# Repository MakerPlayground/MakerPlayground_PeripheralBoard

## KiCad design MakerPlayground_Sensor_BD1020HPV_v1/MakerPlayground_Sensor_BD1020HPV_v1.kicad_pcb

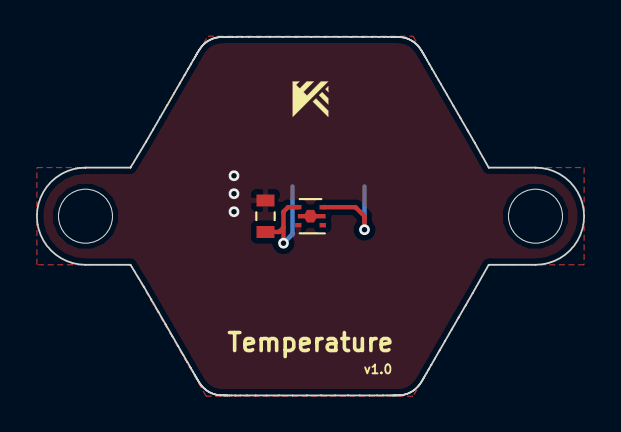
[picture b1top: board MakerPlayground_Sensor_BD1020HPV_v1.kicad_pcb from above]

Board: 2 copper layers, 30.4 x 19.9 mm, 3 parts (1 on the bottom side), 3 nets.

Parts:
C1: 0.1uF; C_0603_1608Metric
J1: Conn_01x04; JST_PH_S4B-PH-SM4-TB_1x04-1MP_P2.00mm_Horizontal
U1: BD1020HFV; HVSOF5

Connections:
GND: C1.2, J1.1, U1.5
unnamed: J1.4, U1.3
VCC: C1.1, J1.2, U1.4

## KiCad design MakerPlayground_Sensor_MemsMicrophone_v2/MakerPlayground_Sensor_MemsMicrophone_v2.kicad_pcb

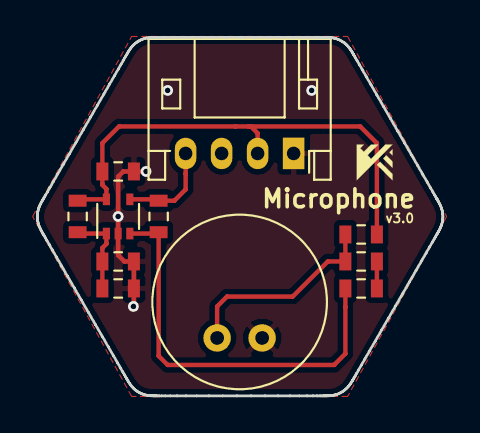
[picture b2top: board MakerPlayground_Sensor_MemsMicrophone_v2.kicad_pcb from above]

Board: 2 copper layers, 22.5 x 19.9 mm, 11 parts (0 on the bottom side), 7 nets.

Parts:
C4, C5: 4.7uF; C_0603_1608Metric
C7: 0.1uF; C_0603_1608Metric
J1: Conn_01x04; JST_PH_S4B-PH-K_1x04_P2.00mm_Horizontal
MK1: 9.7mm; Condenser_Microphone_9.7mm
R1, R2, R3: 10K; R_0603_1608Metric
R4: 820K; R_0603_1608Metric
R5: 2K; R_0603_1608Metric
U2: BD5291FVE-GTR; SOT-353_SC-70-5

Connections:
GND: C5.1, C7.1, J1.1, MK1.2, R3.2, U2.2
unnamed: C4.1, R1.2
unnamed: C4.2, MK1.1, R5.2
unnamed: C5.2, R2.2, R3.1, U2.1
unnamed: R1.1, R4.2, U2.3
Signal: J1.4, R4.1, U2.4
VCC: C7.2, J1.2, R2.1, R5.1, U2.5

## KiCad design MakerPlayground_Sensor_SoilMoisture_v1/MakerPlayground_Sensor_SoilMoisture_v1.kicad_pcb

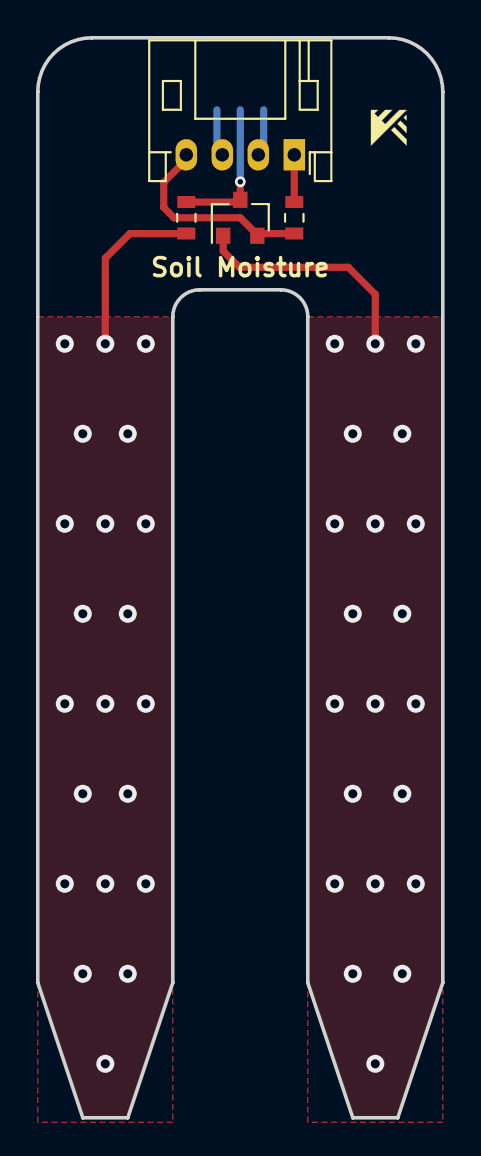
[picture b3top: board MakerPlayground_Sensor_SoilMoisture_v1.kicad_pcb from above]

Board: 2 copper layers, 22.5 x 60.0 mm, 5 parts (1 on the bottom side), 5 nets.

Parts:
J1: Conn_01x04; JST_PH_S4B-PH-K_1x04_P2.00mm_Horizontal
JP1: POWER_SEL; SolderJumper-3_P1.3mm_Bridged12_Pad1.0x1.5mm
Q1: MMBT2222ALT1G; SOT-23
R1: 10K; R_0603_1608Metric
R2: 100; R_0603_1608Metric

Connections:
EN: J1.3, JP1.1
GND: J1.1, R1.2
SIG: J1.4, Q1.2, R1.1
VCC: J1.2, JP1.3
VDD: JP1.2, Q1.3, R2.1
